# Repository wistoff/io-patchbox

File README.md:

# I/O Patchbox

A 3-channel sensor-to-actor controller designed for **Manou Wistoff**'s approach to **phygitale Kunsttherapie**, part of her master thesis at [Alanus Kunsthochschule](https://www.alanus.edu).

Building on the concept of phygitale Kunsttherapie, the I/O Patchbox makes the digital tangible by bringing interactive electronics into the physical space. Interactive electronic components become *material* in the art therapy process, just like clay, paint, or fabric. Through process-oriented creating (Tinkering), clients combine classical crafting materials with sensors and actors connected through the I/O Patchbox, resulting in interactive artworks.

The I/O Patchbox is built on an ESP32-S3 Mini with a custom carrier PCB. Each channel auto-detects its sensor type at boot (ultrasonic HC-SR04 or capacitive touch) and drives an output (LED, motor) proportionally via PWM through a low-side NPN transistor stage.

## How it works

- **3 sensor inputs** (TRRS jacks) carrying power, trigger, echo, and ground
- **3 actor outputs** (TRRS jacks) with 5V PWM low-side switch (2N2222 + flyback diode), load adapted in cable
- **Mode switch** to enable/disable all outputs and trigger recalibration
- **Auto-detect** probes each channel for ultrasonic echoes and falls back to touch if none are found
- Ultrasonic: brightness inversely proportional to distance (0-60 cm)
- Touch: brightness proportional to capacitive contact, with adaptive baseline and asymmetric smoothing

## Project structure

```
i-o-patchbox/
├── firmware/
│   ├── esp32s3-mini/            # current target (LOLIN ESP32-S3 Mini)
│   │   ├── src/main.cpp
│   │   ├── platformio.ini
│   │   └── PINOUT.md
│   └── esp32-wroom-dev-board/   # earlier prototype (ESP32 WROOM DevKit)
│       ├── src/main.cpp
│       ├── platformio.ini
│       └── PINOUT.md
├── hardware/                    # KiCad 10 PCB project
│   ├── pcb.kicad_sch             # schematic
│   ├── pcb.kicad_pcb             # board layout (single-sided, home-etched)
│   ├── pcb.kicad_pro             # project file
│   ├── libs/PJ-320A/             # TRRS jack symbol + footprint library
│   ├── gerber/                   # fabrication outputs
│   ├── exports/                  # SVG renders, drill maps
│   ├── backups/                  # KiCad auto-backups
│   └── schaltplan.pdf            # schematic export
└── enclosure/                   # 3D-printable cases (OBJ)
    ├── cable-plug.obj            # cable strain relief (used by all sensors and actors)
    ├── patchbox/                 # main device enclosure
    │   ├── top.obj
    │   ├── bottom.obj
    │   └── indicator.obj
    ├── sensors/                  # sensor housings
    │   ├── ultrasonic-top.obj
    │   └── ultrasonic-bottom.obj
    └── actors/                   # actor housings
        ├── dc-motor-top.obj
        ├── dc-motor-bottom.obj
        ├── vibration-motor-top.obj
        ├── vibration-motor-bottom.obj
        └── led.obj
```

## Pin assignment (ESP32-S3 Mini)

| Channel | Trigger / Touch | Echo  | Actor |
|---------|-----------------|-------|-------|
| 1       | GP1             | GP7   | GP10  |
| 2       | GP2             | GP8   | GP11  |
| 3       | GP3             | GP9   | GP12  |
| Switch  | -               | -     | GP13  |

## Sensors

All sensors connect via 4-pole TRRS jacks (PJ-320D). Wiring: Tip = +5V, Ring1 = TRIG, Ring2 = ECHO, Sleeve = GND.

Each channel auto-detects its sensor type at startup by probing for ultrasonic echoes. If none are found, it falls back to capacitive touch.

| Type | Part | How it works |
|------|------|--------------|
| **Ultrasonic** | HC-SR04 | Distance sensor (2-60 cm). All 4 TRRS conductors used. Output brightness is inversely proportional to distance. |
| **Capacitive touch** | Bare wire / crocodile cable | Connects to the ECHO pin (Ring2) only. Touch value increases on contact (ESP32-S3 behavior). Adaptive baseline with asymmetric smoothing. Slow ramp-up absorbs motor-stop noise while fast ramp-down keeps release responsive. Recalibrates each time the switch is toggled on. |

## Actors

All actors connect via TRRS jacks. Wiring: Tip = +5V (always on), Sleeve = transistor collector (PWM-switched ground). Ring1/Ring2 unused.

The board provides a generic 5V PWM low-side driver per channel (2N2222 + 330R base resistor + 1N4007 flyback diode). The load type is adapted in the device cable with a series resistor, so no board changes are needed to swap between LEDs and motors.

| Load | Cable resistor | Notes |
|------|----------------|-------|
| **LED** (red/yellow) | 150R series | ~20 mA at 5V, polarity matters (anode to Tip) |
| **LED** (green/blue/white) | 100R series | Higher Vf, ~18 mA |
| **5V motor** | none | Direct connection, bare cable |
| **3V vibration motor** | none | Runs off 5V directly, no series resistor |

PWM runs at 25 kHz (inaudible for motors), 8-bit resolution (0-255).

## Building firmware

Requires [PlatformIO](https://platformio.org/).

```sh
cd firmware/esp32s3-mini
pio run -t upload
pio device monitor
```

## Hardware

Single-sided carrier PCB designed in KiCad 10 for home etching (toner transfer). All copper on F.Cu, SMD TRRS jacks, THT passives soldered from the top side.

Key components: 3x PJ-320D TRRS jacks (sensor), 3x PJ-320D (actor), 3x 2N2222 NPN transistors, 3x 330R base resistors, 3x 1N4007 flyback diodes.

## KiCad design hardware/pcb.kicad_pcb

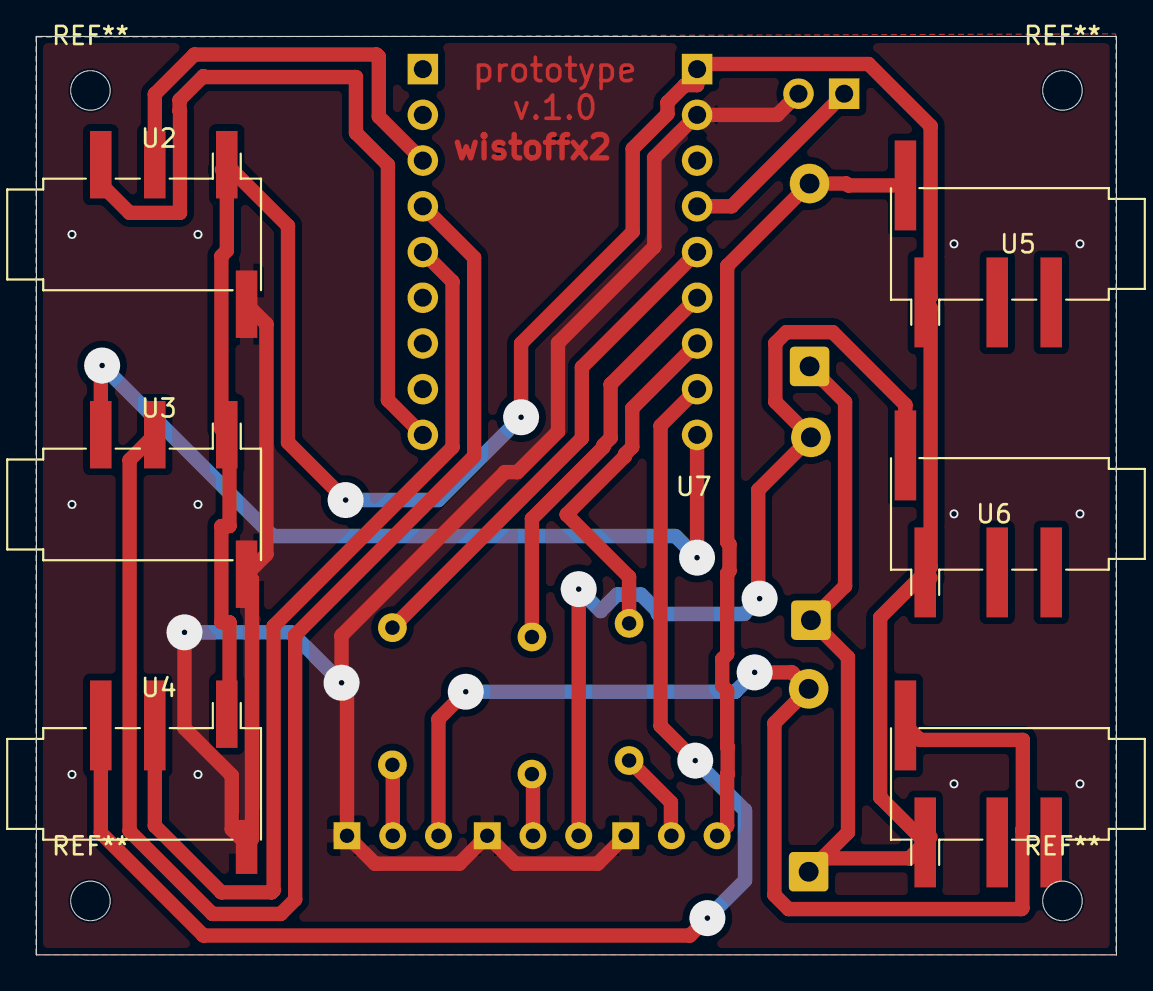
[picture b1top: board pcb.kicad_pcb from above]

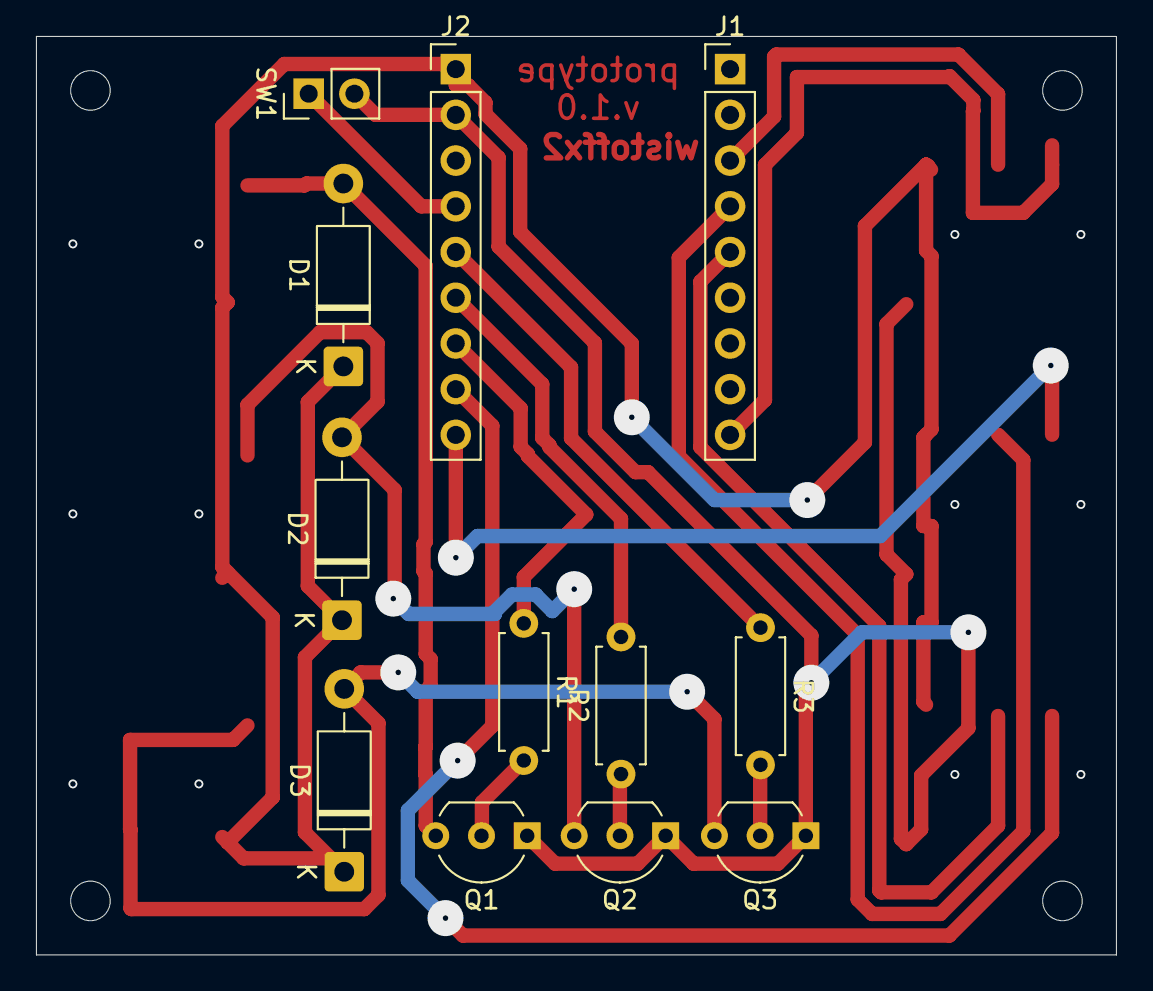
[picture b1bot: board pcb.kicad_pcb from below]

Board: 2 copper layers, 60.0 x 51.0 mm, 18 parts (12 on the bottom side), 2 nets.

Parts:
D1, D2, D3: 1N4007; D_DO-41_SOD81_P10.16mm_Horizontal
J1, J2: Conn_01x11; PinHeader_1x09_P2.54mm_Vertical
Q1, Q2, Q3: 2N2222; TO-92_Inline_Wide
R1, R2, R3: R; R_Axial_DIN0207_L6.3mm_D2.5mm_P7.62mm_Horizontal
SW1: SW_SPST; PinHeader_1x02_P2.54mm_Vertical
U2, U3, U4, U5, U6, U7: PJ-320A; PJ-320D_SMD_remap

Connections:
+5V: U2.2 (Tip), U3.2 (Tip), U4.2 (Tip), U5.2 (Tip), U6.2 (Tip), U7.2 (Tip)
GND: U2.1 (Sleeve), U3.1 (Sleeve), U4.1 (Sleeve)
